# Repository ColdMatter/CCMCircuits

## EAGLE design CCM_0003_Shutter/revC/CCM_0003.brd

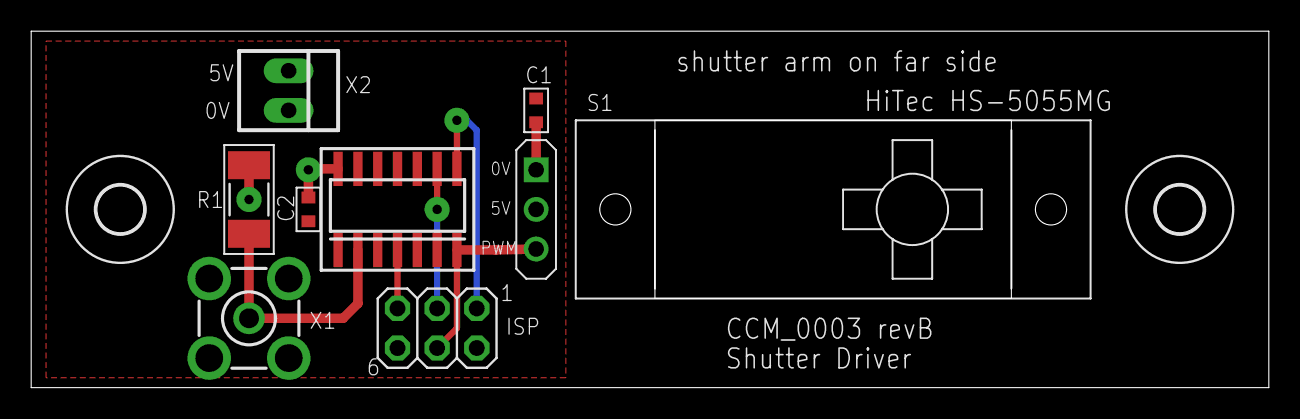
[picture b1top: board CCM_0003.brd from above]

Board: 2 copper layers, 79.4 x 22.9 mm, 10 parts (0 on the bottom side), 7 nets.

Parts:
C1, C2: 10uF; 0603
ISP: ISP; 2X03
MCU: ATTINY24ASO14; SO14
R1: 50; R2010
S1: HS-5055MG
U$1, U$3: 3,0
X1: BU-SMA-H
X2: 22-23-2021

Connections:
!RESET: ISP.5, MCU.4
+5V: C1.1, C2.1, ISP.2, MCU.1, S1.PWR, X2.1
GND: C1.2, C2.2, ISP.6, MCU.14, R1.1, S1.GND, X1.2, X1.3, X1.4, X1.5, X2.2
MISO: ISP.1, MCU.8
MOSI: ISP.4, MCU.7, S1.PWM
SCLK: ISP.3, MCU.9
TTL: MCU.2, R1.2, X1.1

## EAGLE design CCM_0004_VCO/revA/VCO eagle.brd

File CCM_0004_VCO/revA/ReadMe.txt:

This is the initial VCO design (by Ben Sauer).

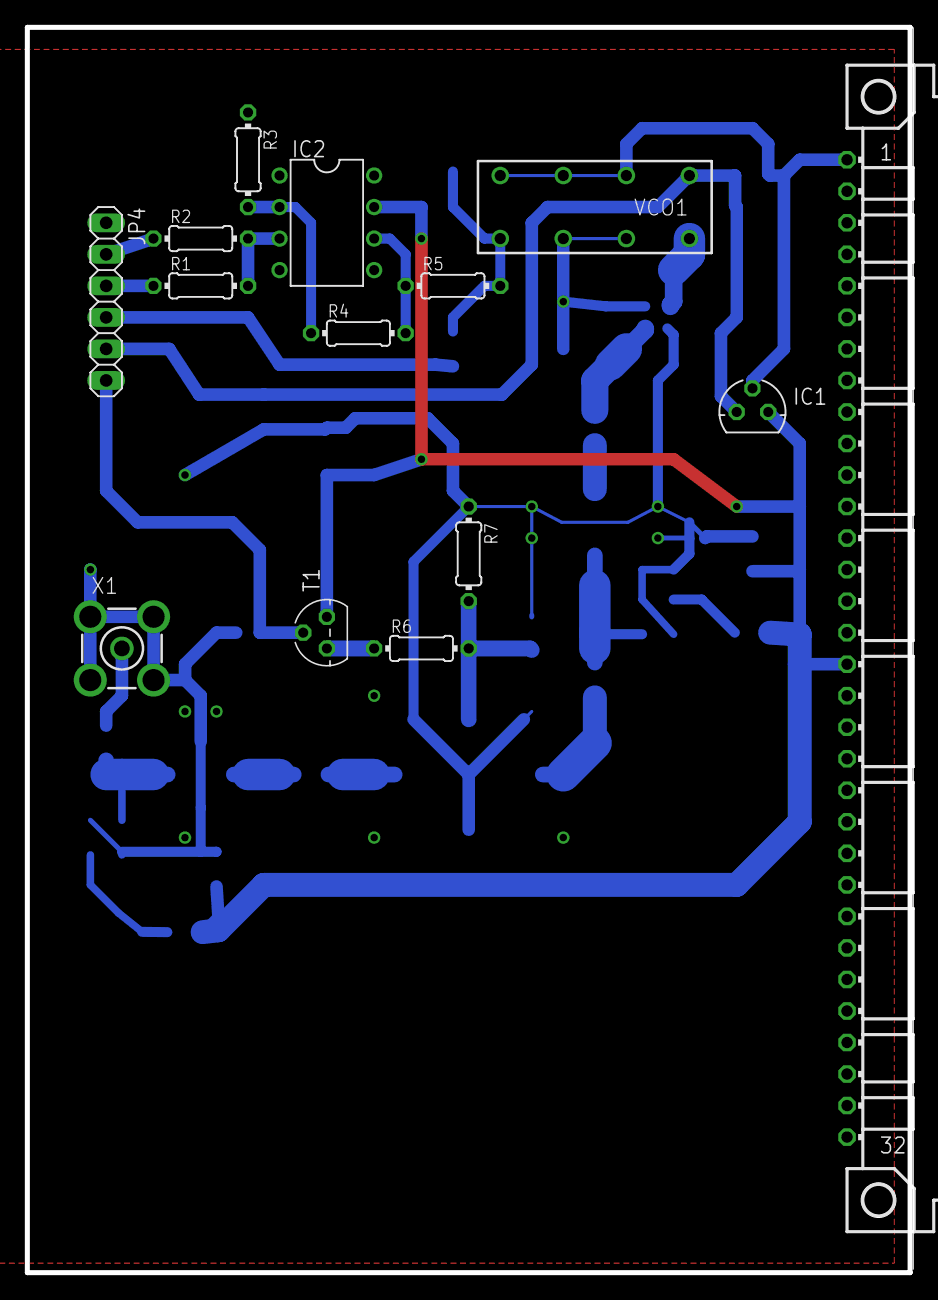
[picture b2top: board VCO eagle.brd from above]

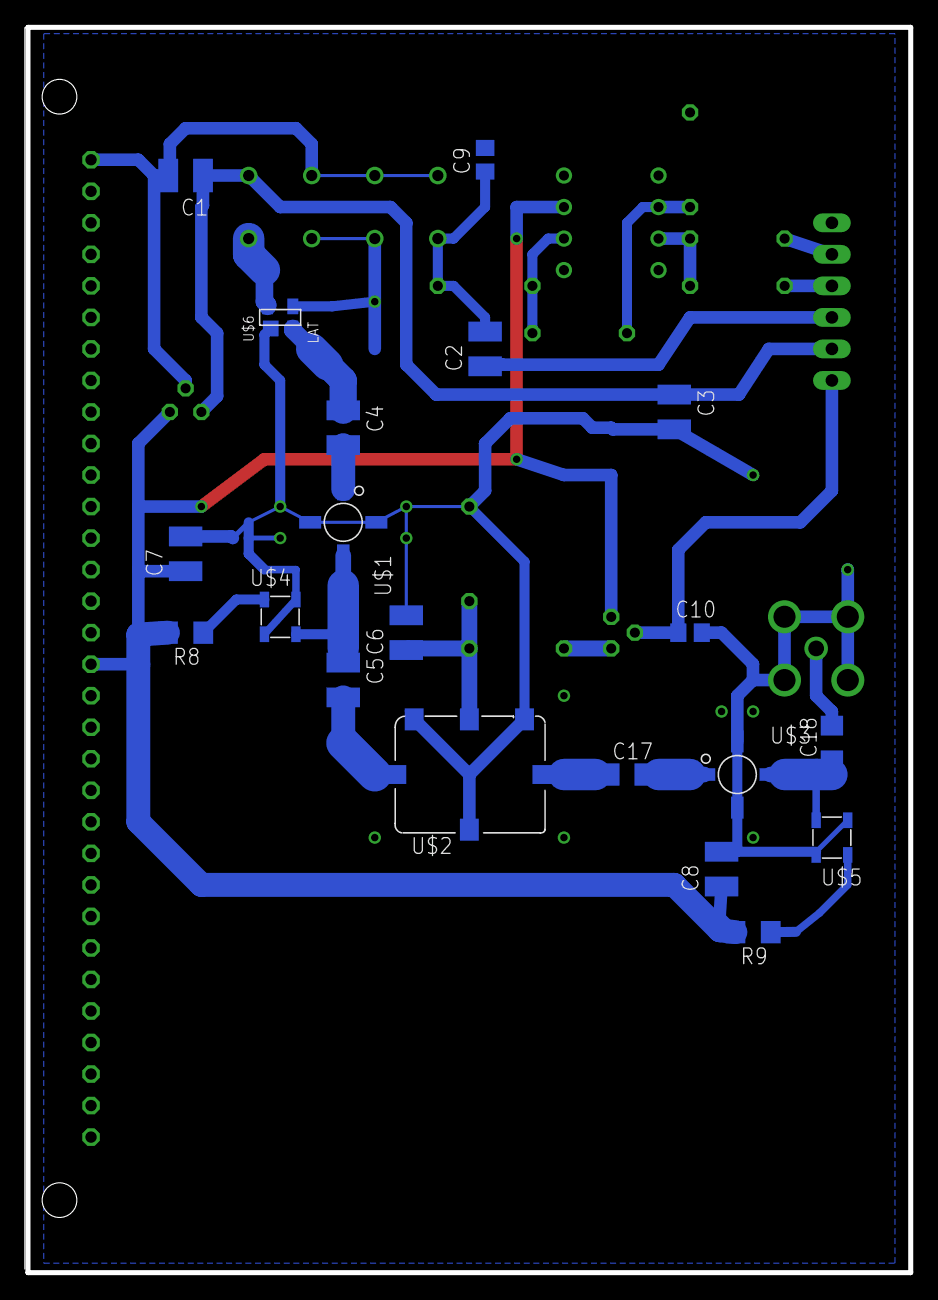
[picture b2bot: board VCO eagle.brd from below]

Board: 2 copper layers, 71.1 x 100.3 mm, 34 parts (20 on the bottom side), 24 nets.

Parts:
C1, C2, C3, C4, C5, C6, C7, C8: 0.1; C1210
C9: 100pF; C0805
C10: 1000pF; C0805
C17, C18: 0.1; C1206
IC1: 78L12; 78LXX
IC2: CA3140N; DIL08
JP4: 1X06
R1, R2, R3, R4, R5: 10k; 0204/7
R6: 500; 0204/7
R7: 50; 0204/7
R8: 270; R1206
R9: 180; R1206
T1: 2N3904; TO92
U$1: MAR3; MAR
U$2: SYAS-1; TTT166
U$3: MAV11; MAR
U$4, U$5: TCCH-80; PL-147
U$6: LAT; MMM168
VCO1: A01
X1: BU-SMA-V
X2: MAB32

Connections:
+12V: C1.1, C3.1, IC1.OUT, JP4.5, VCO1.1
+15V: C7.1, C8.1, IC1.IN, IC2.7, R8.2, R9.2, T1.1, X2.A17
AMP: C10.1, JP4.6, T1.2
GND: C1.2, C3.2, C6.2, C7.2, C8.2, C9.2, C10.2, IC1.GND, IC2.4, JP4.1, R3.1, R7.1, U$1.G2, U$1.G4, U$2.G4, U$2.G5, U$2.G6, U$3.G2, U$3.G4, U$4.2, U$4.4, U$5.2, U$5.4, U$6.P$2, U$6.P$4, VCO1.3, VCO1.4, VCO1.5, VCO1.6, VCO1.7, X1.2, X1.3, X1.4, X1.5, X2.A1, X2.A32
unnamed: R6.1, T1.3
unnamed: JP4.2, R2.1
unnamed: IC2.3, R1.2, R2.2
unnamed: IC2.2, R3.2, R4.1
unnamed: IC2.6, R4.2, R5.1
unnamed: C6.1, R6.2, R7.2, U$2.CTRL
unnamed: C2.1, JP4.4
unnamed: C2.2, C9.1, R5.2, VCO1.8
unnamed: R9.1, U$5.1
unnamed: U$6.P$1, VCO1.2
unnamed: C4.1, U$6.P$3
unnamed: C4.2, U$1.IN
unnamed: C5.1, U$1.OUT/VCC, U$4.3
unnamed: C5.2, U$2.IN
unnamed: C17.2, U$3.IN
unnamed: C18.1, U$3.OUT/VCC, U$5.3
unnamed: R8.1, U$4.1
unnamed: C17.1, U$2.OUT
unnamed: C18.2, X1.1
unnamed: JP4.3, R1.1

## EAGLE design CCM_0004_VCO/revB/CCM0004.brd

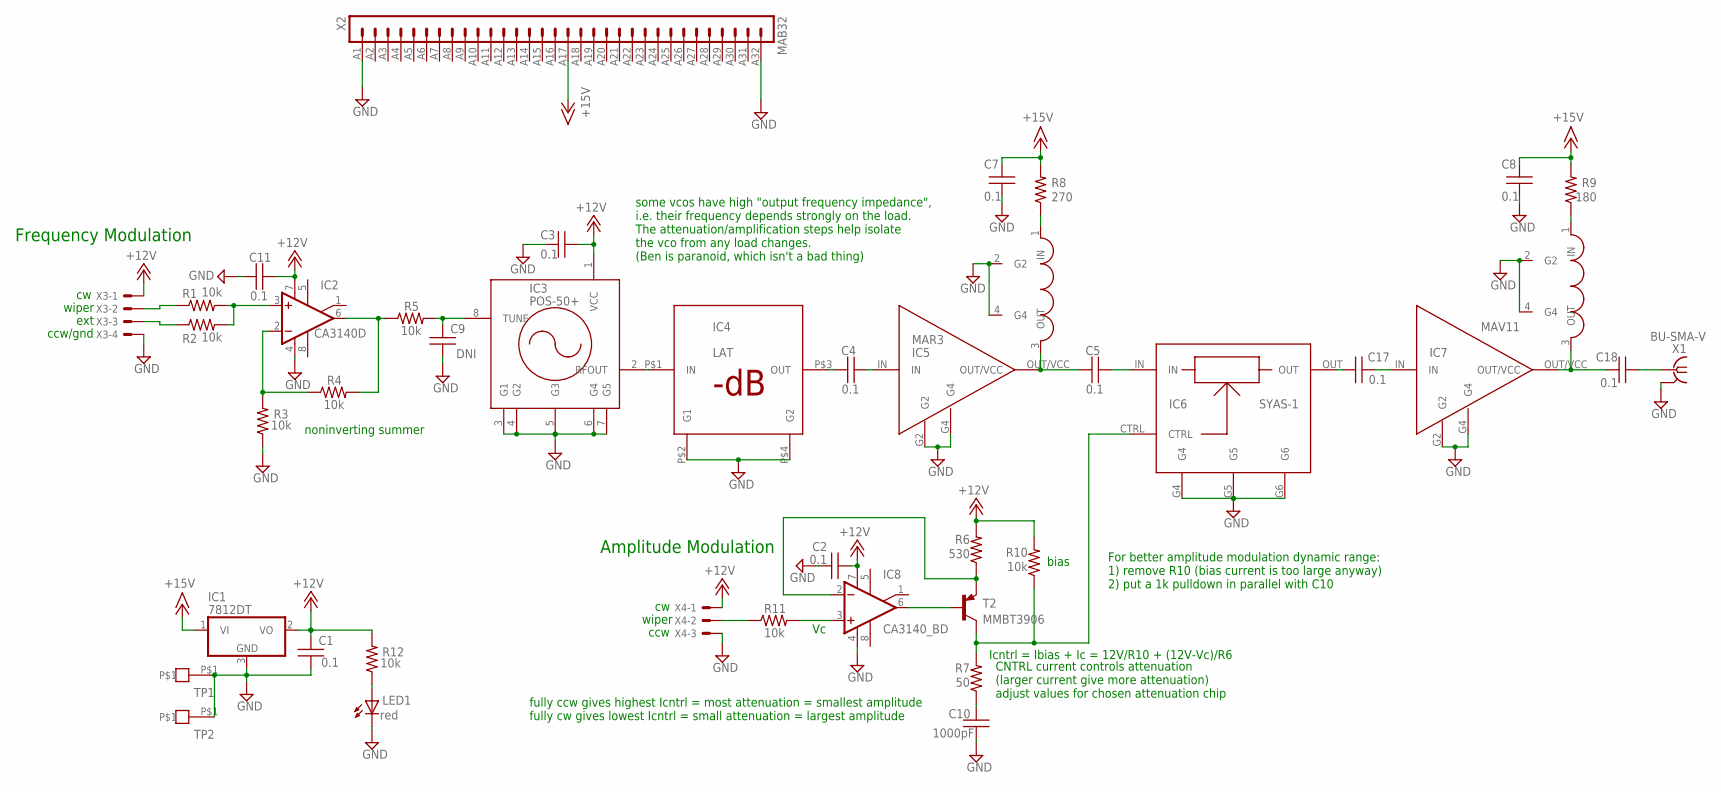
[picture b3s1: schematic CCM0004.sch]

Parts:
C1, C2, C3, C7, C8, C11: 0.1; 0603
C4, C5, C17, C18: 0.1; 2010
C9: DNI; 0603
C10: 1000pF; 2010
IC1: 7812DT; TO252
IC2: CA3140D; SO08
IC3: POS-50+; A01
IC4: LAT; MMM168
IC5: MAR3; MAR
IC6: SYAS-1; TTT166
IC7: MAV11; MAR
IC8: CA3140_BD; SO08
L1, L2: TCCH-80; PL-147
LED1: red; CHIPLED_0603
R1, R2, R3, R4, R5, R11, R12: 10k; 0603
R6: 530; 2010
R7: 50; 2010
R8: 270; 2010
R9: 180; 2010
R10: 10k; 2010
T2: MMBT3906; SOT23-BEC
TP1, TP2: TESTPOINT
X1: BU-SMA-V
X2: MAB32
X3: 22-23-2041
X4: 22-23-2031

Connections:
+12V: C1.1, C2.2, C3.1, C11.2, IC1.2 (VO), IC2.7 (V+), IC3.1 (VCC), IC8.7 (V+), R6.2, R10.2, R12.2, X3.1, X4.1
+15V: C7.1, C8.1, IC1.1 (VI), R8.2, R9.2, X2.A17 (17)
GND: C1.2, C2.1, C3.2, C7.2, C8.2, C9.2, C10.1, C11.1, IC1.3 (GND), IC2.4 (V-), IC3.3 (G1), IC3.4 (G2), IC3.5 (G3), IC3.6 (G4), IC3.7 (G5), IC4.P$2 (G1), IC4.P$4 (G2), IC5.G2, IC5.G4, IC6.G4, IC6.G5, IC6.G6, IC7.G2, IC7.G4, IC8.4 (V-), L1.2 (G2), L1.4 (G4), L2.2 (G2), L2.4 (G4), LED1.C, R3.1, TP1.P$1, TP2.P$1, X1.2 (GND), X1.3 (GND), X1.4 (GND), X1.5 (GND), X2.A1 (1), X2.A32 (32), X3.4, X4.3
unnamed: IC8.6 (OUT), T2.B
unnamed: IC8.2 (-IN), R6.1, T2.E
unnamed: C10.2, R7.1
unnamed: R1.1, X3.2
unnamed: IC6.CTRL, R7.2, R10.1, T2.C
unnamed: R2.1, X3.3
unnamed: R11.1, X4.2
unnamed: IC8.3 (+IN), R11.2
unnamed: LED1.A, R12.1
unnamed: IC2.3 (+IN), R1.2, R2.2
unnamed: IC2.2 (-IN), R3.2, R4.1
unnamed: IC2.6 (OUT), R4.2, R5.1
unnamed: C9.1, IC3.8 (TUNE), R5.2
unnamed: L2.1 (IN), R9.1
unnamed: IC3.2 (RFOUT), IC4.P$1 (IN)
unnamed: C4.1, IC4.P$3 (OUT)
unnamed: C4.2, IC5.IN
unnamed: C5.1, IC5.OUT/VCC, L1.3 (OUT)
unnamed: C5.2, IC6.IN
unnamed: C17.2, IC7.IN
unnamed: C18.1, IC7.OUT/VCC, L2.3 (OUT)
unnamed: L1.1 (IN), R8.1
unnamed: C17.1, IC6.OUT
unnamed: C18.2, X1.1

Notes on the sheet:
wiper
noninverting summer
some vcos have high "output frequency impedance", i.e. their frequency depends strongly on the load. The attenuation/amplification steps help isolate the vco from any load changes. (Ben is paranoid, which isn't a bad thing)
bias
ccw/gnd
ext
ccw
Amplitude Modulation
Frequency Modulation
CNTRL current controls attenuation (larger current give more attenuation) adjust values for chosen attenuation chip
Icntrl = Ibias + Ic = 12V/R10 + (12V-Vc)/R6
fully ccw gives highest Icntrl = most attenuation = smallest amplitude fully cw gives lowest Icntrl = small attenuation = largest amplitude
For better amplitude modulation dynamic range: 1) remove R10 (bias current is too large anyway) 2) put a 1k pulldown in parallel with C10

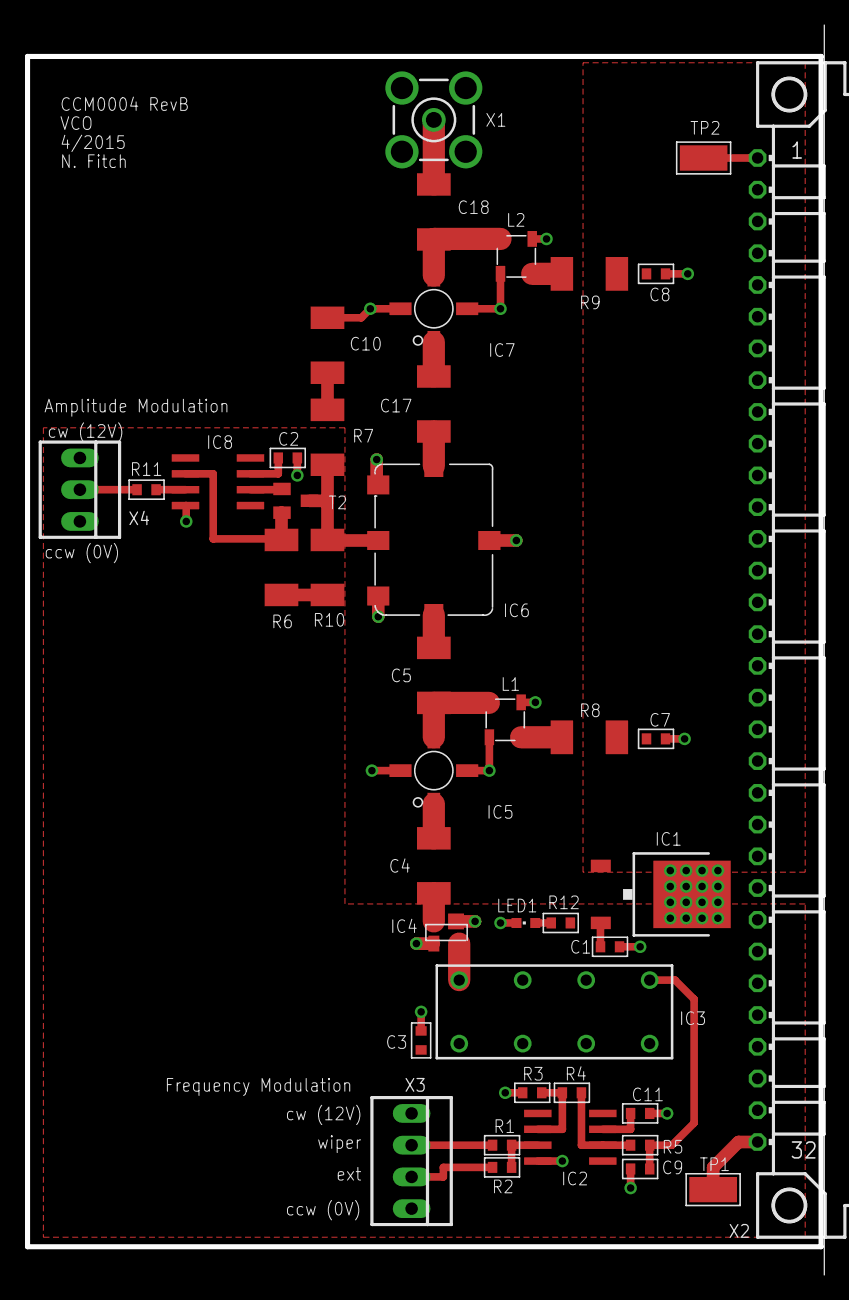
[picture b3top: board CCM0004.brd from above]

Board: 2 copper layers, 63.8 x 100.0 mm, 42 parts (0 on the bottom side), 27 nets.

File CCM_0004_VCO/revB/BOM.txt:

Partlist exported from C:/Users/nfitch/Google Drive/Imperial/Electronics/CCM_0004_VCO/revB/CCM0004.sch at 07/05/2015 15:25:44

Qty Value      Device          Package      Parts                        Description                                                MF    MPN        OC_FARNELL OC_NEWARK
6   0.1        CAPACITOR0603   0603         C1, C2, C3, C7, C8, C11                                                                                                      
4   0.1        CAPACITOR2010   2010         C4, C5, C17, C18                                                                                                             
1   1000pF     CAPACITOR2010   2010         C10                                                                                                                          
1   100pF      CAPACITOR0603   0603         C9                                                                                                                           
7   10k        RESISTOR0603    0603         R1, R2, R3, R4, R5, R11, R12 RESISTOR, American symbol                                                                       
1   10k        RESISTOR2010    2010         R10                          RESISTOR, American symbol                                                                       
1   180        RESISTOR2010    2010         R9                           RESISTOR, American symbol                                                                       
1   22-23-2031 22-23-2031      22-23-2031   X4                           .100" (2.54mm) Center Header - 3 Pin                       MOLEX 22-23-2031 1462950    30C0862  
1   22-23-2041 22-23-2041      22-23-2041   X3                           .100" (2.54mm) Center Header - 4 Pin                       MOLEX 22-23-2041 1462920    38C0355  
1   270        RESISTOR2010    2010         R8                           RESISTOR, American symbol                                                                       
1   50         RESISTOR2010    2010         R7                           RESISTOR, American symbol                                                                       
1   530        RESISTOR2010    2010         R6                           RESISTOR, American symbol                                                                       
1   7812DT     7812DT          TO252        IC1                          Positive VOLTAGE REGULATOR                                                                      
1   BU-SMA-V   BU-SMA-V        BU-SMA-V     X1                           FEMALE SMA CONNECTOR                                                                            
1   CA3140D    CA3140D         SO08         IC2                          OP AMP                                                                                          
1   CA3140_BD  CA3140_BD       SO08         IC8                          OP AMP                                                                                          
1   LAT        LAT             MMM168       IC4                          Minicircuits surface mount attenuator                                                           
1   MAB32      MAB32           MAB32        X2                           CONNECTOR                                                                                       
1   MAR3       MAR3            MAR          IC5                          MiniCircuits MAR-3+ amplifier                                                                   
1   MAV11      MAV11           MAR          IC7                          MiniCircuits MAV-11 amplifer, currently identical to MAR-3                                      
1   MMBT3906   MMBT3906LT1SMD  SOT23-BEC    T2                           PNP Transistror                                                                                 
1   POS-50+    POS             A01          IC3                          MiniCircuits POS-x VCO, through hole package                                                    
1   SYAS-1     SYAS-1          TTT166       IC6                          MiniCircuits voltage variable attenuator                                                        
2   TCCH-80    TCCH-80         PL-147       L1, L2                       MiniCircuits TCCH-80+ choke                                                                     
2   TESTPOINT  TESTPOINT       TESTPOINT    TP1, TP2                                                                                                                     
1   red        LEDCHIPLED_0603 CHIPLED_0603 LED1                         LED

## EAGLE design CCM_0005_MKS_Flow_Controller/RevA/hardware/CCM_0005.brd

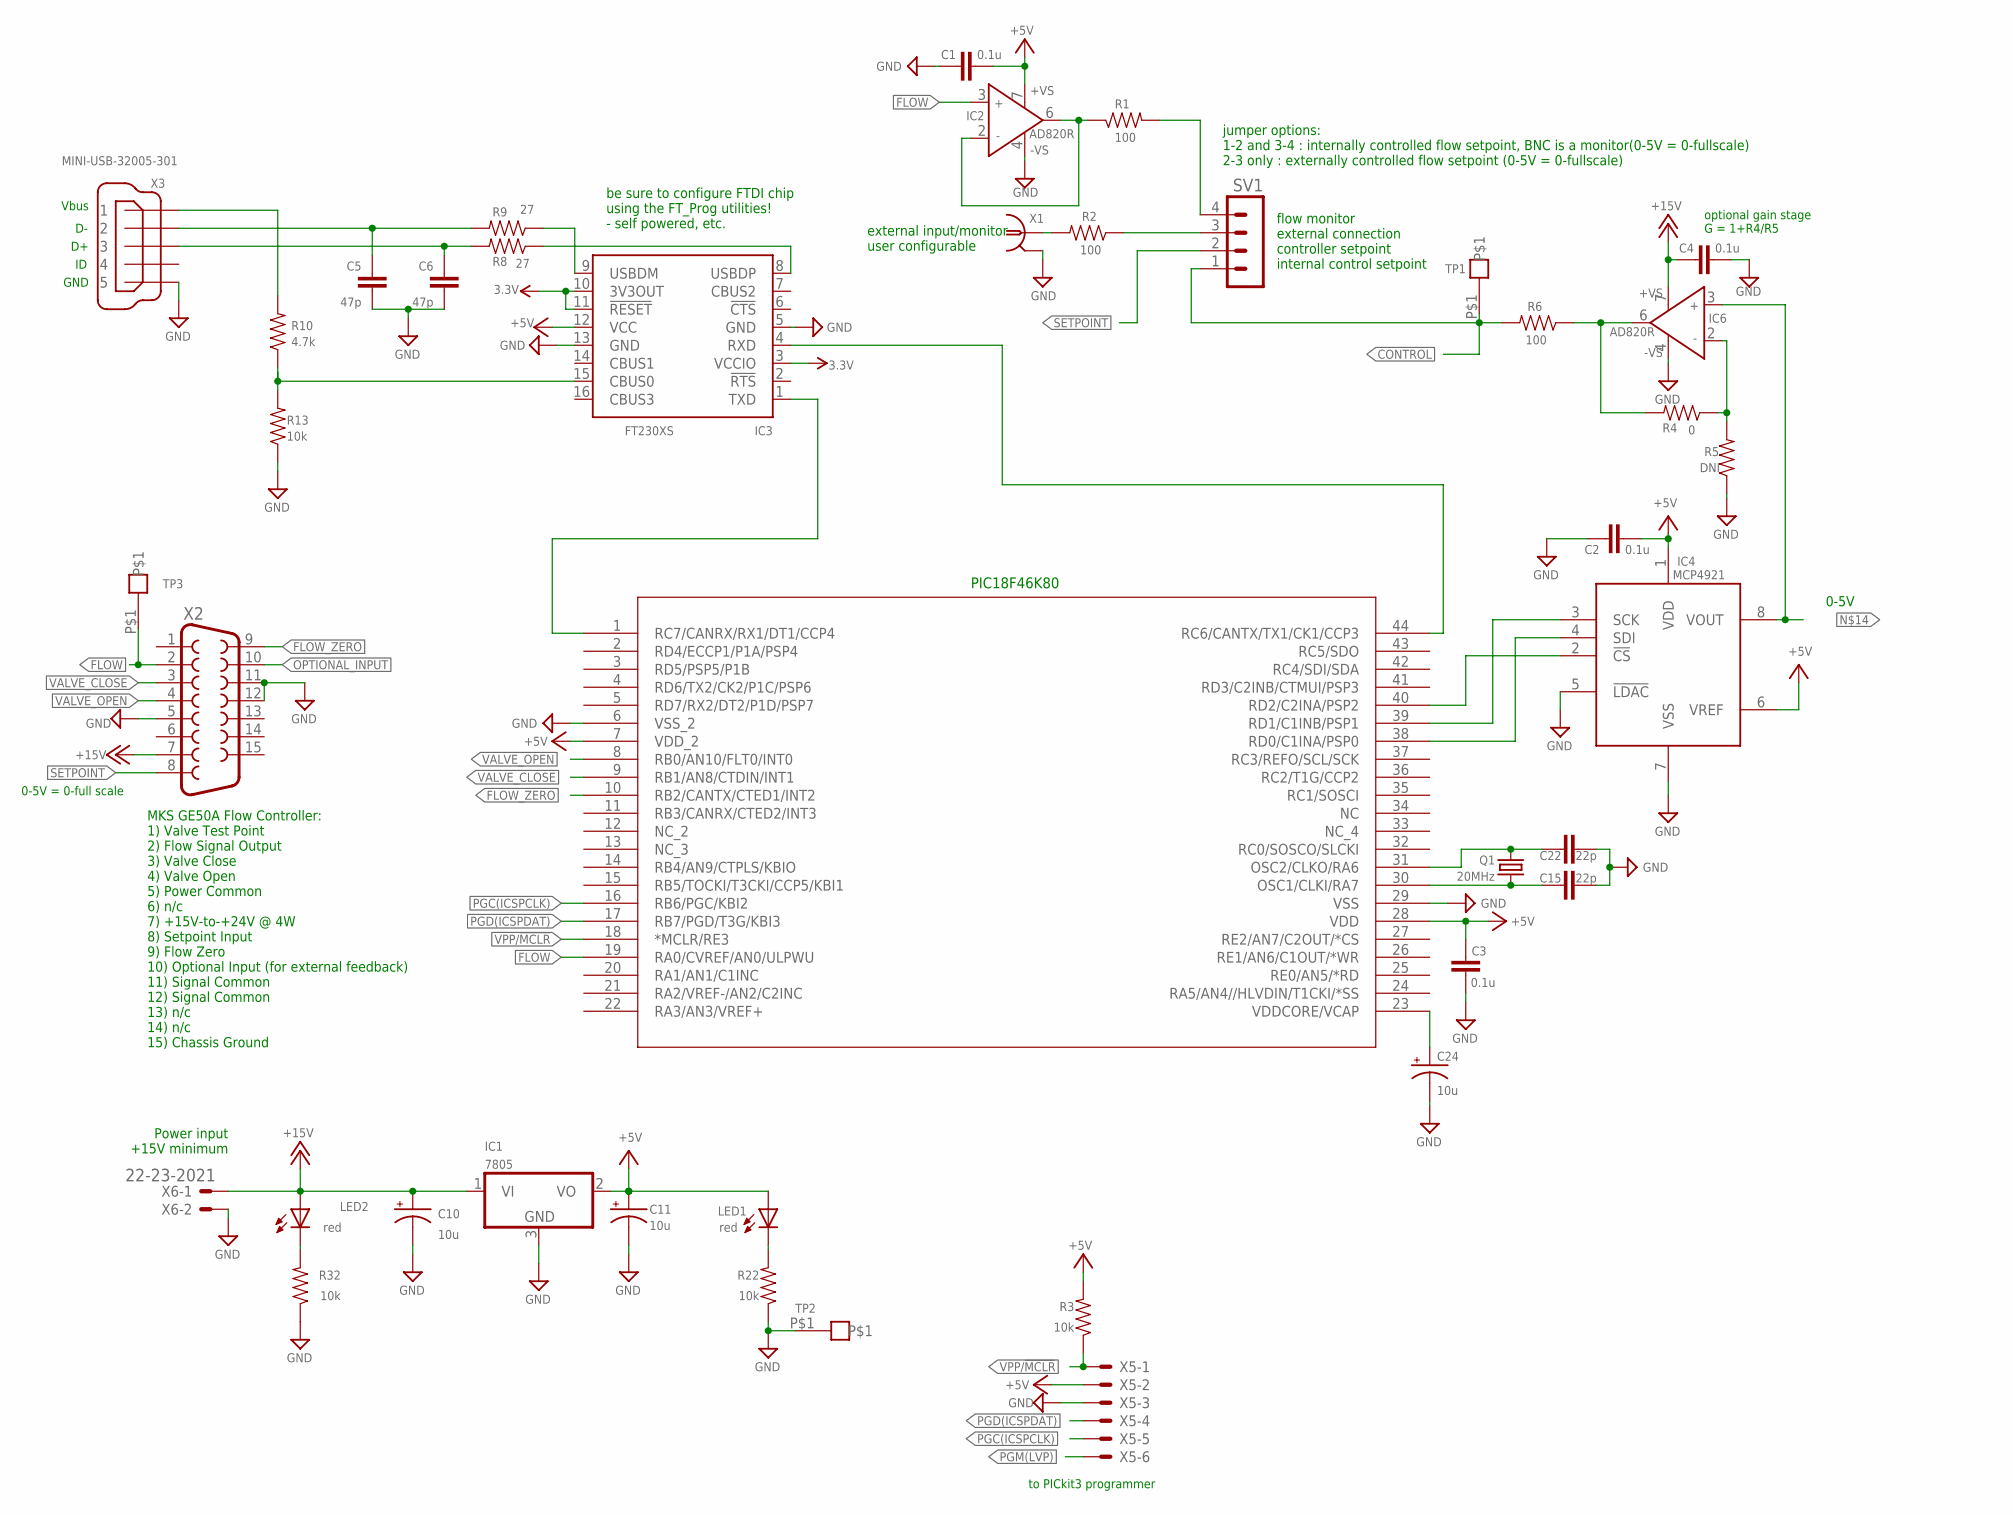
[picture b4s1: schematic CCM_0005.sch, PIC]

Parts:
C1, C2, C3, C4: 0.1u; 0603-CAP
C5, C6: 47p; 0603-CAP
C10, C11, C24: 10u; EIA3216
C15, C22: 22p; 0603-CAP
IC1: 7805; TO252
IC2, IC6: AD820R; SO8
IC3: FT230XS; SSOP16
IC4: MCP4921; SO08
IC5: PIC18F46K80; TQFP44_MC
LED1, LED2: red; CHIPLED_0603
Q1: 20MHz; TC26V
R1, R2, R6: 100; 0603-RES
R3, R13, R22, R32: 10k; 0603-RES
R4: 0; 0603-RES
R5: DNI; 0603-RES
R8, R9: 27; 0603-RES
R10: 4.7k; 0603-RES
SV1: MA04-1
TP1, TP3: control; TESTPOINT
TP2: TESTPOINT
X1: 1-227161-0; AMP_227161
X2: F15HP
X3: MINI-USB-32005-301; 32005-301
X5: 22-23-2061
X6: 22-23-2021

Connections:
3.3V: IC3.3 (VCCIO), IC3.10 (3V3OUT), IC3.11 (!RESET)
+5V: C1.1, C2.1, C3.1, C11.A (+), IC1.2 (VO), IC2.7 (+VS), IC3.12 (VCC), IC4.1 (VDD), IC4.6 (VREF), IC5.7 (VDD_2), IC5.28 (VDD), LED1.A, R3.2, X5.2
+15V: C4.2, C10.A (+), IC1.1 (VI), IC6.7 (+VS), LED2.A, X2.7, X6.1
CONTROL: R6.2, SV1.1, TP1.P$1
D+: C6.1, R8.2, X3.3
D-: C5.1, R9.2, X3.2
FLOW: IC2.3 (IN+), IC5.19 (RA0/CVREF/AN0/ULPWU), TP3.P$1, X2.2
FLOW_ZERO: IC5.10 (RB2/CANTX/CTED1/INT2), X2.9
GND: C1.2, C2.2, C3.2, C4.1, C5.2, C6.2, C10.C (-), C11.C (-), C15.1, C22.1, C24.C (-), IC1.3 (GND), IC2.4 (-VS), IC3.5 (GND), IC3.13 (GND), IC4.5 (!LDAC), IC4.7 (VSS), IC5.6 (VSS_2), IC5.29 (VSS), IC6.4 (-VS), R5.1, R13.1, R22.1, R32.1, TP2.P$1, X1.2, X2.5, X2.11, X2.12, X3.5, X5.3, X6.2
LED1: LED1.C, R22.2
LED5: LED2.C, R32.2
N12: IC6.6 (OUT), R4.2, R6.1
unnamed: R2.2, X1.1
unnamed: R1.2, SV1.4
unnamed: IC2.2 (IN-), IC2.6 (OUT), R1.1
unnamed: C15.2, IC5.30 (OSC1/CLKI/RA7), Q1.1
unnamed: IC3.1 (TXD), IC5.1 (RC7/CANRX/RX1/DT1/CCP4)
unnamed: IC3.9 (USBDM), R9.1
unnamed: IC4.2 (!CS), IC5.40 (RD2/C2INA/PSP2)
unnamed: IC3.8 (USBDP), R8.1
unnamed: R2.1, SV1.3
unnamed: C22.2, IC5.31 (OSC2/CLKO/RA6), Q1.2
unnamed: IC4.3 (SCK), IC5.39 (RD1/C1INB/PSP1)
unnamed: C24.A (+), IC5.23 (VDDCORE/VCAP)
unnamed: IC3.15 (CBUS0), R10.1, R13.2
unnamed: IC4.8 (VOUT), IC6.3 (IN+)
unnamed: IC6.2 (IN-), R4.1, R5.2
unnamed: IC4.4 (SDI), IC5.38 (RD0/C1INA/PSP0)
OPTIONAL_INPUT: X2.10
PGC(ICSPCLK): IC5.16 (RB6/PGC/KBI2), X5.5
PGD(ICSPDAT): IC5.17 (RB7/PGD/T3G/KBI3), X5.4
PGM(LVP): X5.6
SETPOINT: SV1.2, X2.8
TX1: IC3.4 (RXD), IC5.44 (RC6/CANTX/TX1/CK1/CCP3)
VALVE_CLOSE: IC5.9 (RB1/AN8/CTDIN/INT1), X2.3
VALVE_OPEN: IC5.8 (RB0/AN10/FLT0/INT0), X2.4
VBUS: R10.2, X3.1
VPP/!MCLR: IC5.18 (*MCLR/RE3), R3.1, X5.1

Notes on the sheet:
to PICkit3 programmer
Power input +15V minimum
MKS GE50A Flow Controller: 1) Valve Test Point 2) Flow Signal Output 3) Valve Close 4) Valve Open 5) Power Common 6) n/c 7) +15V-to-+24V @ 4W 8) Setpoint Input 9) Flow Zero 10) Optional Input (for external feedback) 11) Signal Common 12) Signal Common 13) n/c 14) n/c 15) Chassis Ground
Vbus
GND
0-5V = 0-full scale
PIC18F46K80
jumper options: 1-2 and 3-4 : internally controlled flow setpoint, BNC is a monitor(0-5V = 0-fullscale) 2-3 only : externally controlled flow setpoint (0-5V = 0-fullscale)
external input/monitor user configurable
0-5V
flow monitor external connection controller setpoint internal control setpoint
be sure to configure FTDI chip using the FT_Prog utilities! - self powered, etc.
optional gain stage G = 1+R4/R5

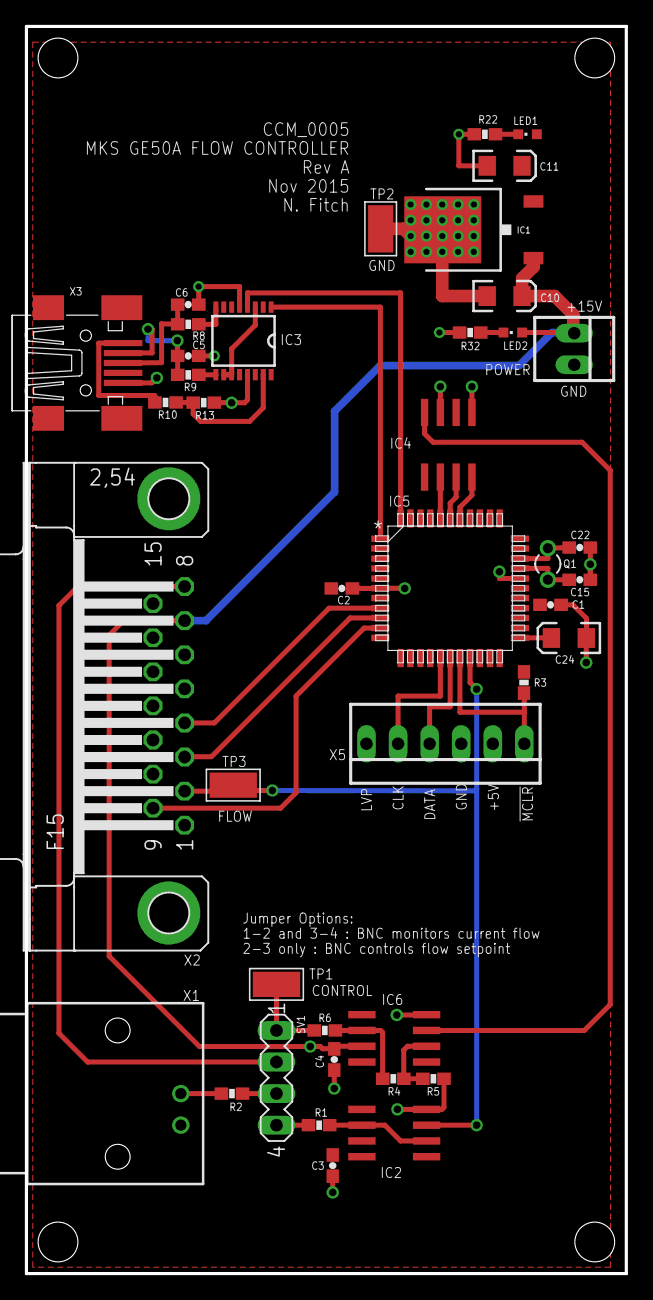
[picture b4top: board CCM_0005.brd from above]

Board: 2 copper layers, 48.3 x 100.3 mm, 41 parts (0 on the bottom side), 36 nets.

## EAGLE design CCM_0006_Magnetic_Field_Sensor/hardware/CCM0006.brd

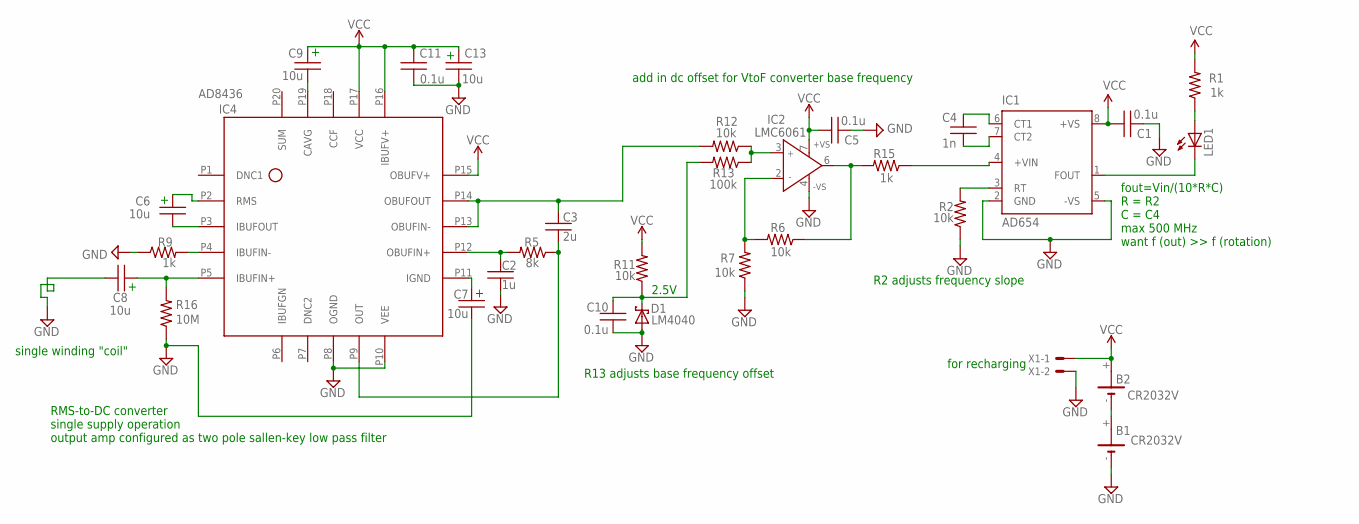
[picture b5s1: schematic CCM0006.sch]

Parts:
B1, B2: CR2032V
C1, C5, C10, C11: 0.1u; 0402
C2: 1u; 0402
C3: 2u; 0402
C4: 1n; 0402
C6, C7, C8, C9, C13: 10u; 0805
D1: LM4040; SOT23
IC1: AD654; SO08
IC2: LMC6061; SO8
IC4: AD8436; CP-20-10
LED1: LED3MM
R1, R9, R15: 1k; 0402
R2, R6, R7, R11, R12: 10k; 0402
R5: 8k; 0402
R13: 100k; 0402
R16: 10M; 0402
X1: 22-23-2021

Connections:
AGND: B1.-, C1.2, C2.1, C5.2, C7.1, C8.1, C10.2, C11.2, C13.1, D1.2 (A), IC1.2 (GND), IC1.5 (-VS), IC2.4 (-VS), IC4.P8 (OGND), IC4.P10 (VEE), R2.1, R7.1, R9.1, R16.1, X1.2
unnamed: LED1.A, R1.1
unnamed: IC1.1 (FOUT), LED1.K (C)
unnamed: IC1.3 (RT), R2.2
unnamed: C4.2, IC1.6 (CT1)
unnamed: C4.1, IC1.7 (CT2)
unnamed: C3.1, IC4.P13 (OBUFIN-), IC4.P14 (OBUFOUT), R12.2
unnamed: C7.2, IC4.P11 (IGND)
unnamed: C2.2, IC4.P12 (OBUFIN+), R5.2
unnamed: IC1.4 (+VIN), R15.1
unnamed: C10.1, D1.1 (C), R11.1, R13.2
unnamed: C3.2, IC4.P9 (OUT), R5.1
unnamed: IC2.2 (IN-), R6.2, R7.2
unnamed: C6.1, IC4.P3 (IBUFOUT)
unnamed: IC2.3 (IN+), R12.1, R13.1
unnamed: IC2.6 (OUT), R6.1, R15.2
unnamed: B1.+, B2.-
unnamed: C8.2, IC4.P5 (IBUFIN+), R16.2
unnamed: IC4.P4 (IBUFIN-), R9.2
unnamed: C9.2, IC4.P19 (CAVG)
RMS: C6.2, IC4.P2 (RMS)
VCC: B2.+, C1.1, C5.1, C9.1, C11.1, C13.2, IC1.8 (+VS), IC2.7 (+VS), IC4.P15 (OBUFV+), IC4.P16 (IBUFV+), IC4.P17 (VCC), R1.2, R11.2, X1.1

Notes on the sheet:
2.5V
R13 adjusts base frequency offset
fout=Vin/(10*R*C) R = R2 C = C4 max 500 MHz want f (out) >> f (rotation)
RMS-to-DC converter single supply operation output amp configured as two pole sallen-key low pass filter
R2 adjusts frequency slope
add in dc offset for VtoF converter base frequency
single winding "coil"
for recharging

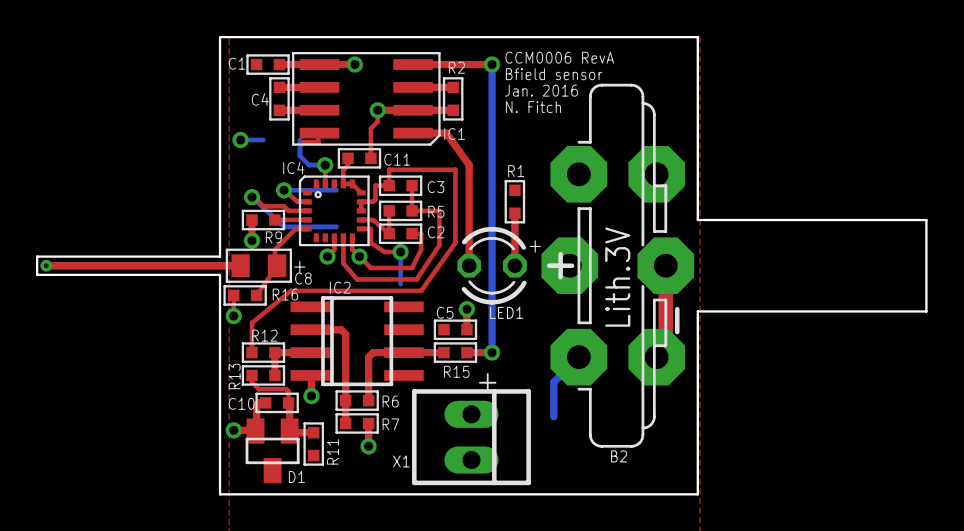
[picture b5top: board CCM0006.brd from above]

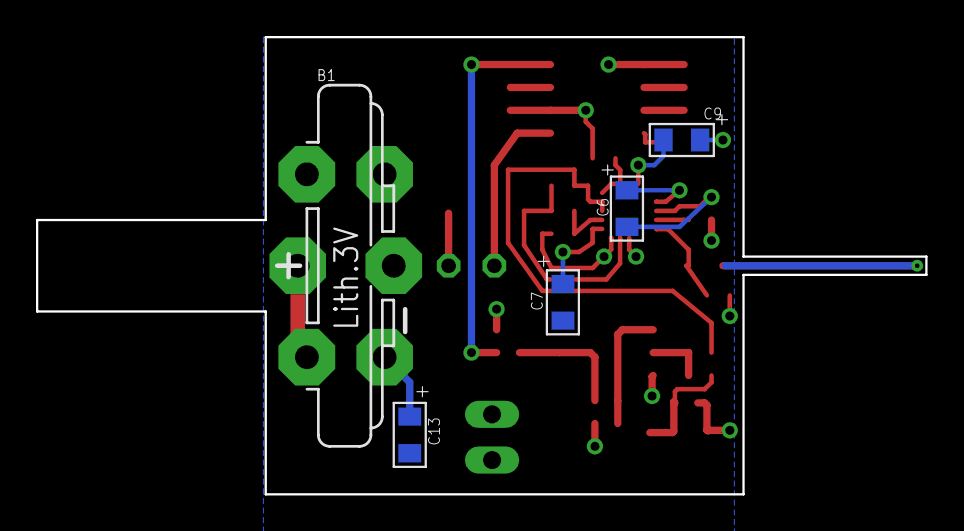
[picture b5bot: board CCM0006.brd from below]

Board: 2 copper layers, 49.4 x 25.4 mm, 31 parts (5 on the bottom side), 22 nets.

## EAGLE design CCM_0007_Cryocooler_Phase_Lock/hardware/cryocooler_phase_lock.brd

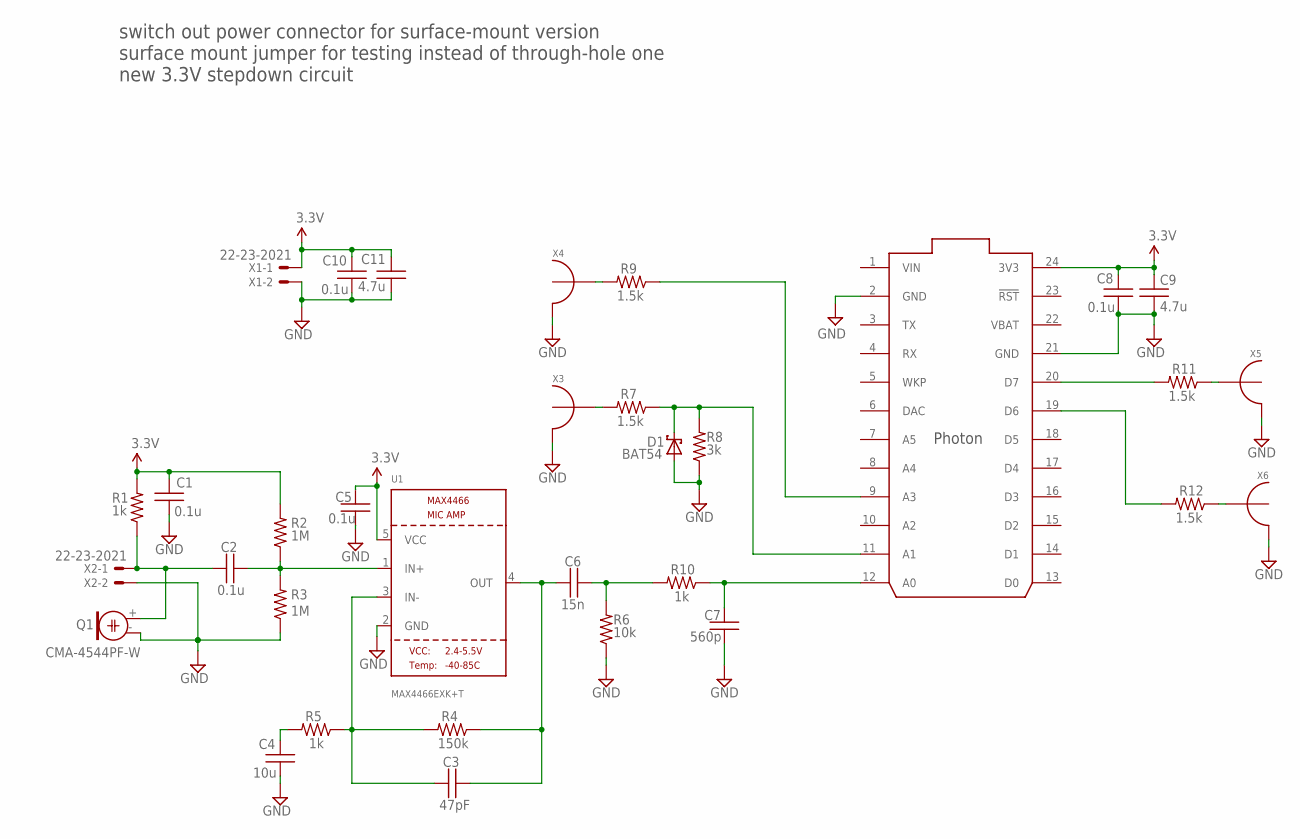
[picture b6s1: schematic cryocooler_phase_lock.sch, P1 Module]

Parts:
C1, C2, C5, C8, C10: 0.1u; 0603
C3: 47pF; 0603
C4: 10u; 0603
C6: 15n; 0603
C7: 560p; 0603
C9, C11: 4.7u; 0805
D1: BAT54; SOT23
Q1: CMA-4544PF-W; ELECTRET_9.7
R1, R5, R10: 1k; 0603
R2, R3: 1M; 0603
R4: 150k; 0603
R6: 10k; 0603
R7, R9, R11, R12: 1.5k; 0603
R8: 3k; 0603
U1: MAX4466EXK+T; SC70-5
U3: PHOTON_WITH_HEADERS; PHOTON
X1, X2: 22-23-2021
X3, X4, X5, X6: BNC_VERTICAL

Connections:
3.3V: C1.1, C5.1, C8.1, C9.2, C10.1, C11.2, R1.2, R2.2, U1.5 (VCC), U3.24 (3V3), X1.1
AUDIO_IN: C3.2, C6.1, R4.1, U1.4 (OUT)
DELAY_ADJUST: R7.2, X3.SIGNAL
GND: C1.2, C4.2, C5.2, C7.2, C8.2, C9.1, C10.2, C11.1, D1.1 (A), Q1.- (1), R3.1, R6.1, R8.1, U1.2 (GND), U3.2 (GND), U3.21 (GND), X1.2, X2.2, X3.GND, X4.GND, X5.GND, X6.GND
N10: D1.3 (C), R7.1, R8.2, U3.11 (A1)
unnamed: C2.1, Q1.+ (2), R1.1, X2.1
unnamed: C2.2, R2.1, R3.2, U1.1 (IN+)
unnamed: C3.1, R4.2, R5.1, U1.3 (IN-)
unnamed: C4.1, R5.2
unnamed: C6.2, R6.2, R10.2
unnamed: C7.1, R10.1, U3.12 (A0)
unnamed: R9.1, U3.9 (A3)
unnamed: R11.2, U3.20 (D7)
unnamed: R12.2, U3.19 (D6)
SYNC_OUT: R11.1, X5.SIGNAL
TRIGGER_OUT: R12.1, X6.SIGNAL
VBAT: U3.22 (VBAT)
VIN: U3.1 (VIN)
VOLUME_INDICATOR: R9.2, X4.SIGNAL

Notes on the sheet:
switch out power connector for surface-mount version surface mount jumper for testing instead of through-hole one new 3.3V stepdown circuit

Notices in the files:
parts and their libraries:
microbuilder: This work is placed in the public domain, and may be freely used for commercial and non-commercial work with the following conditions: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
